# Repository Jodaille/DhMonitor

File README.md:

# DhMonitor
[Kicad][1] project using Arduino pro mini for beehive monitoring

[1]: http://kicad-pcb.org/

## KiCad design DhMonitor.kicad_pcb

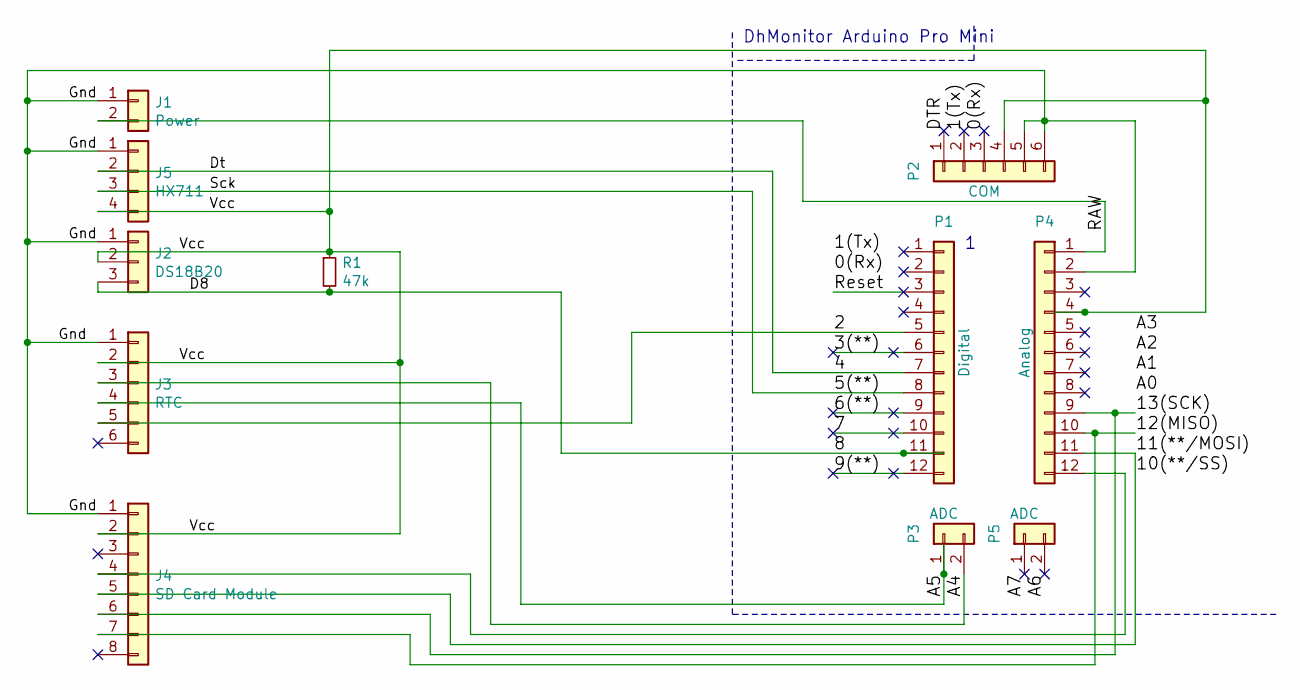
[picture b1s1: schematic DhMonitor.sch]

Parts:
J1: Power; PinHeader_1x02_P2.54mm_Horizontal
J2: DS18B20; PinHeader_1x03_P2.54mm_Vertical
J3: RTC; PinHeader_1x06_P2.54mm_Vertical
J4: SD Card Module; PinHeader_1x08_P2.54mm_Vertical
J5: HX711; PinHeader_1x04_P2.54mm_Vertical
P1: Digital; Socket_Strip_Arduino_1x12
P2: COM; Socket_Strip_Arduino_1x06
P3, P5: ADC; Socket_Strip_Arduino_1x02
P4: Analog; Socket_Strip_Arduino_1x12
R1: 47k; R_LDR_4.9x4.2mm_P2.54mm_Vertical

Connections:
/0(Rx): P2.3
/1(Tx): P2.2
/2: J3.5, P1.5
/3(**): P1.6
/4: J5.2, P1.7
/5(**): J5.3, P1.8
/6(**): P1.9
/7: P1.10
/8: J2.3, P1.11, R1.2
/9(**): P1.12
/10(**/SS): J4.5, P4.11
/12(MISO): J4.7, P4.10
/13(SCK): J4.6, P4.9
/A4: J3.3, P3.2
/A5: J3.4, P3.1
/A6: P5.2
/A7: P5.1
/DTR: P2.1
/Gnd: J1.1, J2.1, J3.1, J4.1, J5.1, P2.5, P2.6, P4.2
/RAW: J1.2, P4.1
/Reset: P1.3
/Vcc: J2.2, J3.2, J4.2, J5.4, P2.4, P4.4, R1.1
unnamed: J4.4, P4.12

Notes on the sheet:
DhMonitor Arduino Pro Mini

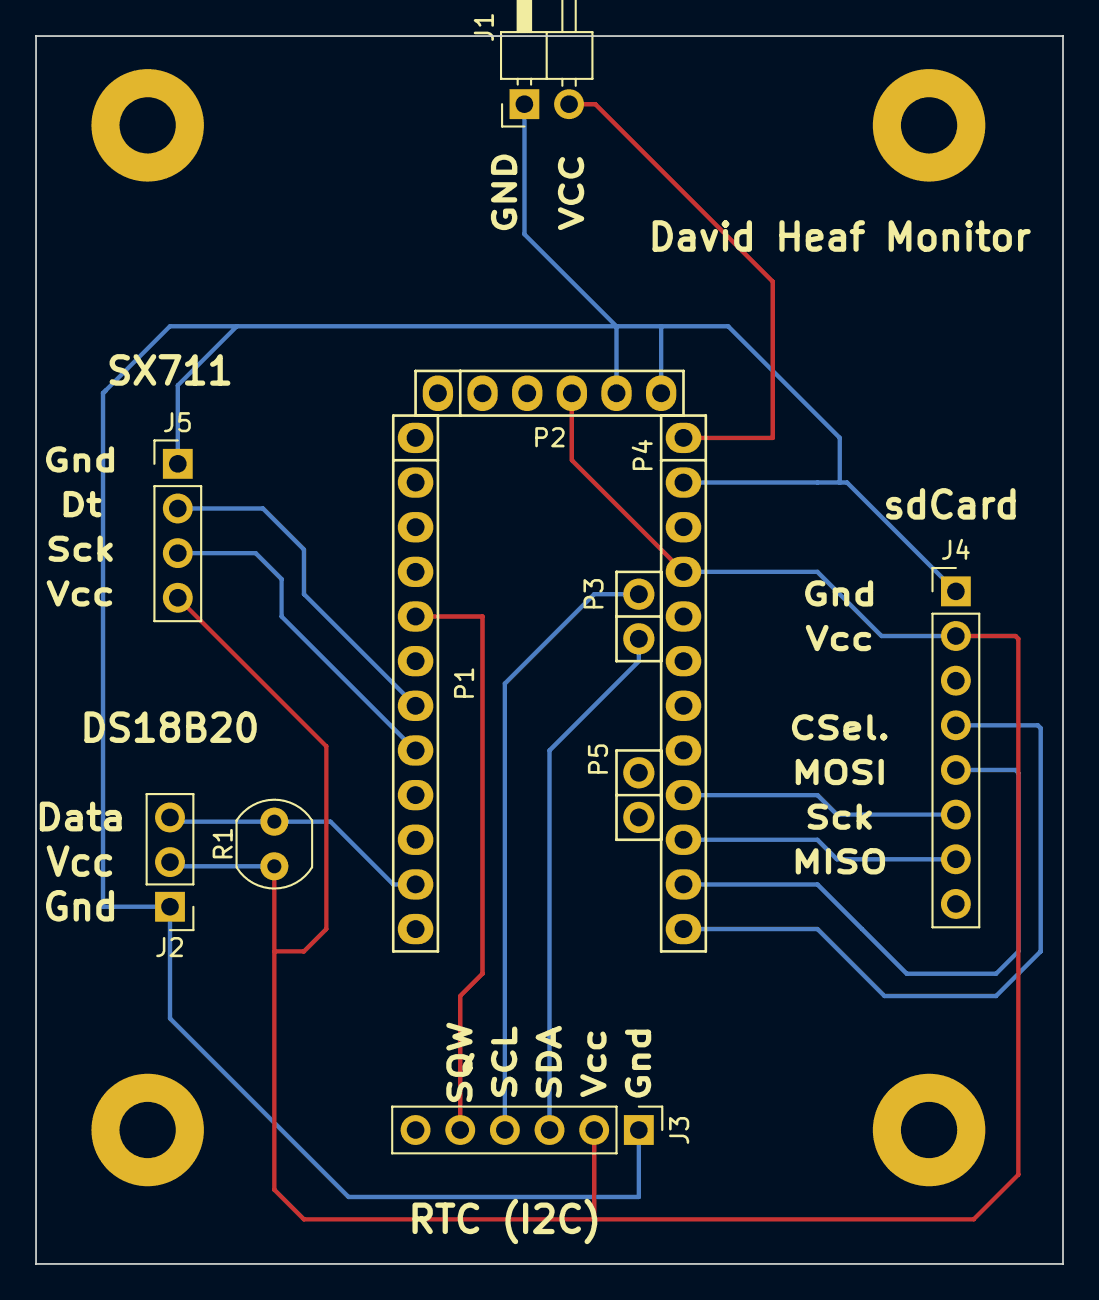
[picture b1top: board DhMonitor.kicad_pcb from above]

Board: 2 copper layers, 58.4 x 69.9 mm, 11 parts (0 on the bottom side), 13 nets.

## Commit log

2019-03-26 First prototype of DHMonitor PCB with Kicad
2019-03-26 add rendered PCB image to README
2019-03-26 solves image path :o
2019-03-26 solves wrong files :o
2019-03-26 v0.2: add labels + mounting holes + hx711 pinouts
2019-04-16 add rendered view of v0.2
